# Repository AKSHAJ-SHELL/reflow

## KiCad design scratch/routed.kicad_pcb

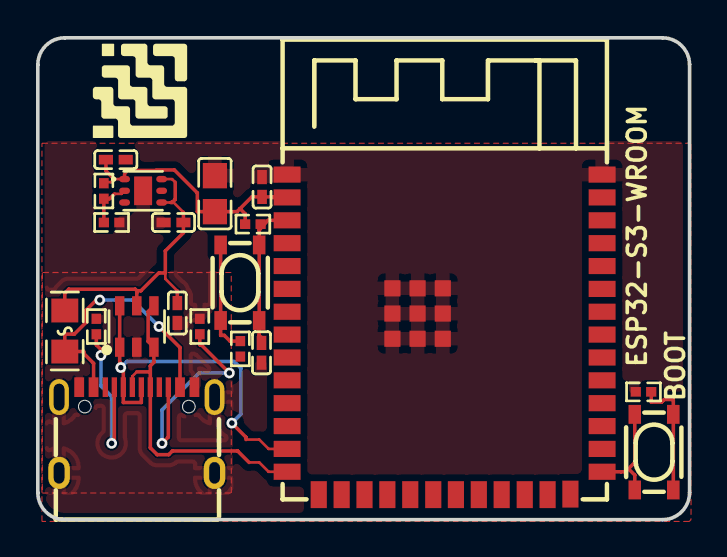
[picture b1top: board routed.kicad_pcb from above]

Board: 2 copper layers, 36.2 x 26.8 mm, 20 parts (0 on the bottom side), 13 nets.

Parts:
C1, C2, C10: 1µF ±10% 25V X5R; C0402
C3, C8: 100nF ±10% 16V X7R; C0402
C9: 22µF ±20% 6.3V X5R; C0805
D1: SOT-23-6_L2.9-W1.6-P0.95-LS2.8-BL
F1: F0805
R1, R3: 10kΩ ±1% 62.5mW; R0402
R2, R4: 100Ω ±1% 62.5mW; R0402
R5: 47kΩ ±1% 62.5mW; R0402
R6, R7: 5.1kΩ ±1% 62.5mW; R0402
SW1, SW2: KEY-SMD_4P-L4.2-W3.2-P2.20-LS4.6
U2: WIRELM-SMD_ESP32-S3-WROOM-1
U3: WSON-6_L2.0-W2.0-P0.65-TL-EP
USB1: USB-C-SMD_TYPE-C-6PIN-2MD-073

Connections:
GND: C1.2, C2.2, C3.2, C8.2, C9.2, C10.2, D1.2, R1.2, R2.2, R4.2, R6.2, R7.2, U2.1, U2.40, U2.41, U3.3, U3.7, USB1.1, USB1.12, USB1.13, USB1.14, USB1.15, USB1.16
USB_D_N: D1.1, D1.6, U2.13, USB1.5, USB1.7
USB_D_P: D1.3, D1.4, U2.14, USB1.6, USB1.8
VDIV_OUTPUT: R1.1, R5.2, U3.2
button-input-input-0: R2.1, SW1.1, SW1.2
button-input-input-1: R4.1, SW2.1, SW2.2
cc[0]-line: R6.1, USB1.4
cc[1]-line: R7.1, USB1.10
gpios[0]-output: SW1.3, SW1.4, U2.27
output-output: C10.1, R3.1, SW2.3, SW2.4, U2.3
power-VCC: C2.1, C8.1, C9.1, R3.2, R5.1, U2.2, U3.1
power_in-VCC: C1.1, C3.1, D1.5, F1.2, U3.4, U3.6
power_vbus-VCC: F1.1, USB1.2, USB1.11

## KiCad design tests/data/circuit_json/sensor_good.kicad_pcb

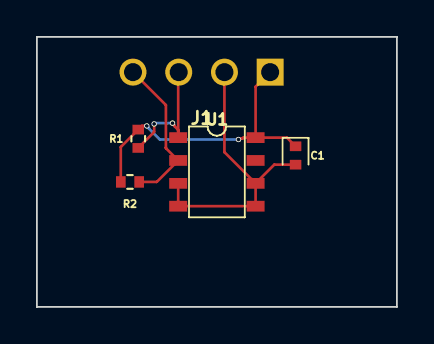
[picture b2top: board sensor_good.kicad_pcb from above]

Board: 2 copper layers, 20.0 x 15.0 mm, 5 parts (0 on the bottom side), 4 nets.

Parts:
C1: 100nF; capacitor_cap0402
J1: J1; pin_header_pinrow4_nopinlabels
R1, R2: 4.7kΩ; resistor_res0402
U1: chip_soic8

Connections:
GND: C1.2, J1.2, U1.3, U1.4, U1.5, U1.6
SCL: J1.4, R2.1, U1.2
SDA: J1.3, R1.1, U1.1
V3_3: C1.1, J1.1, R1.2, R2.2, U1.8
